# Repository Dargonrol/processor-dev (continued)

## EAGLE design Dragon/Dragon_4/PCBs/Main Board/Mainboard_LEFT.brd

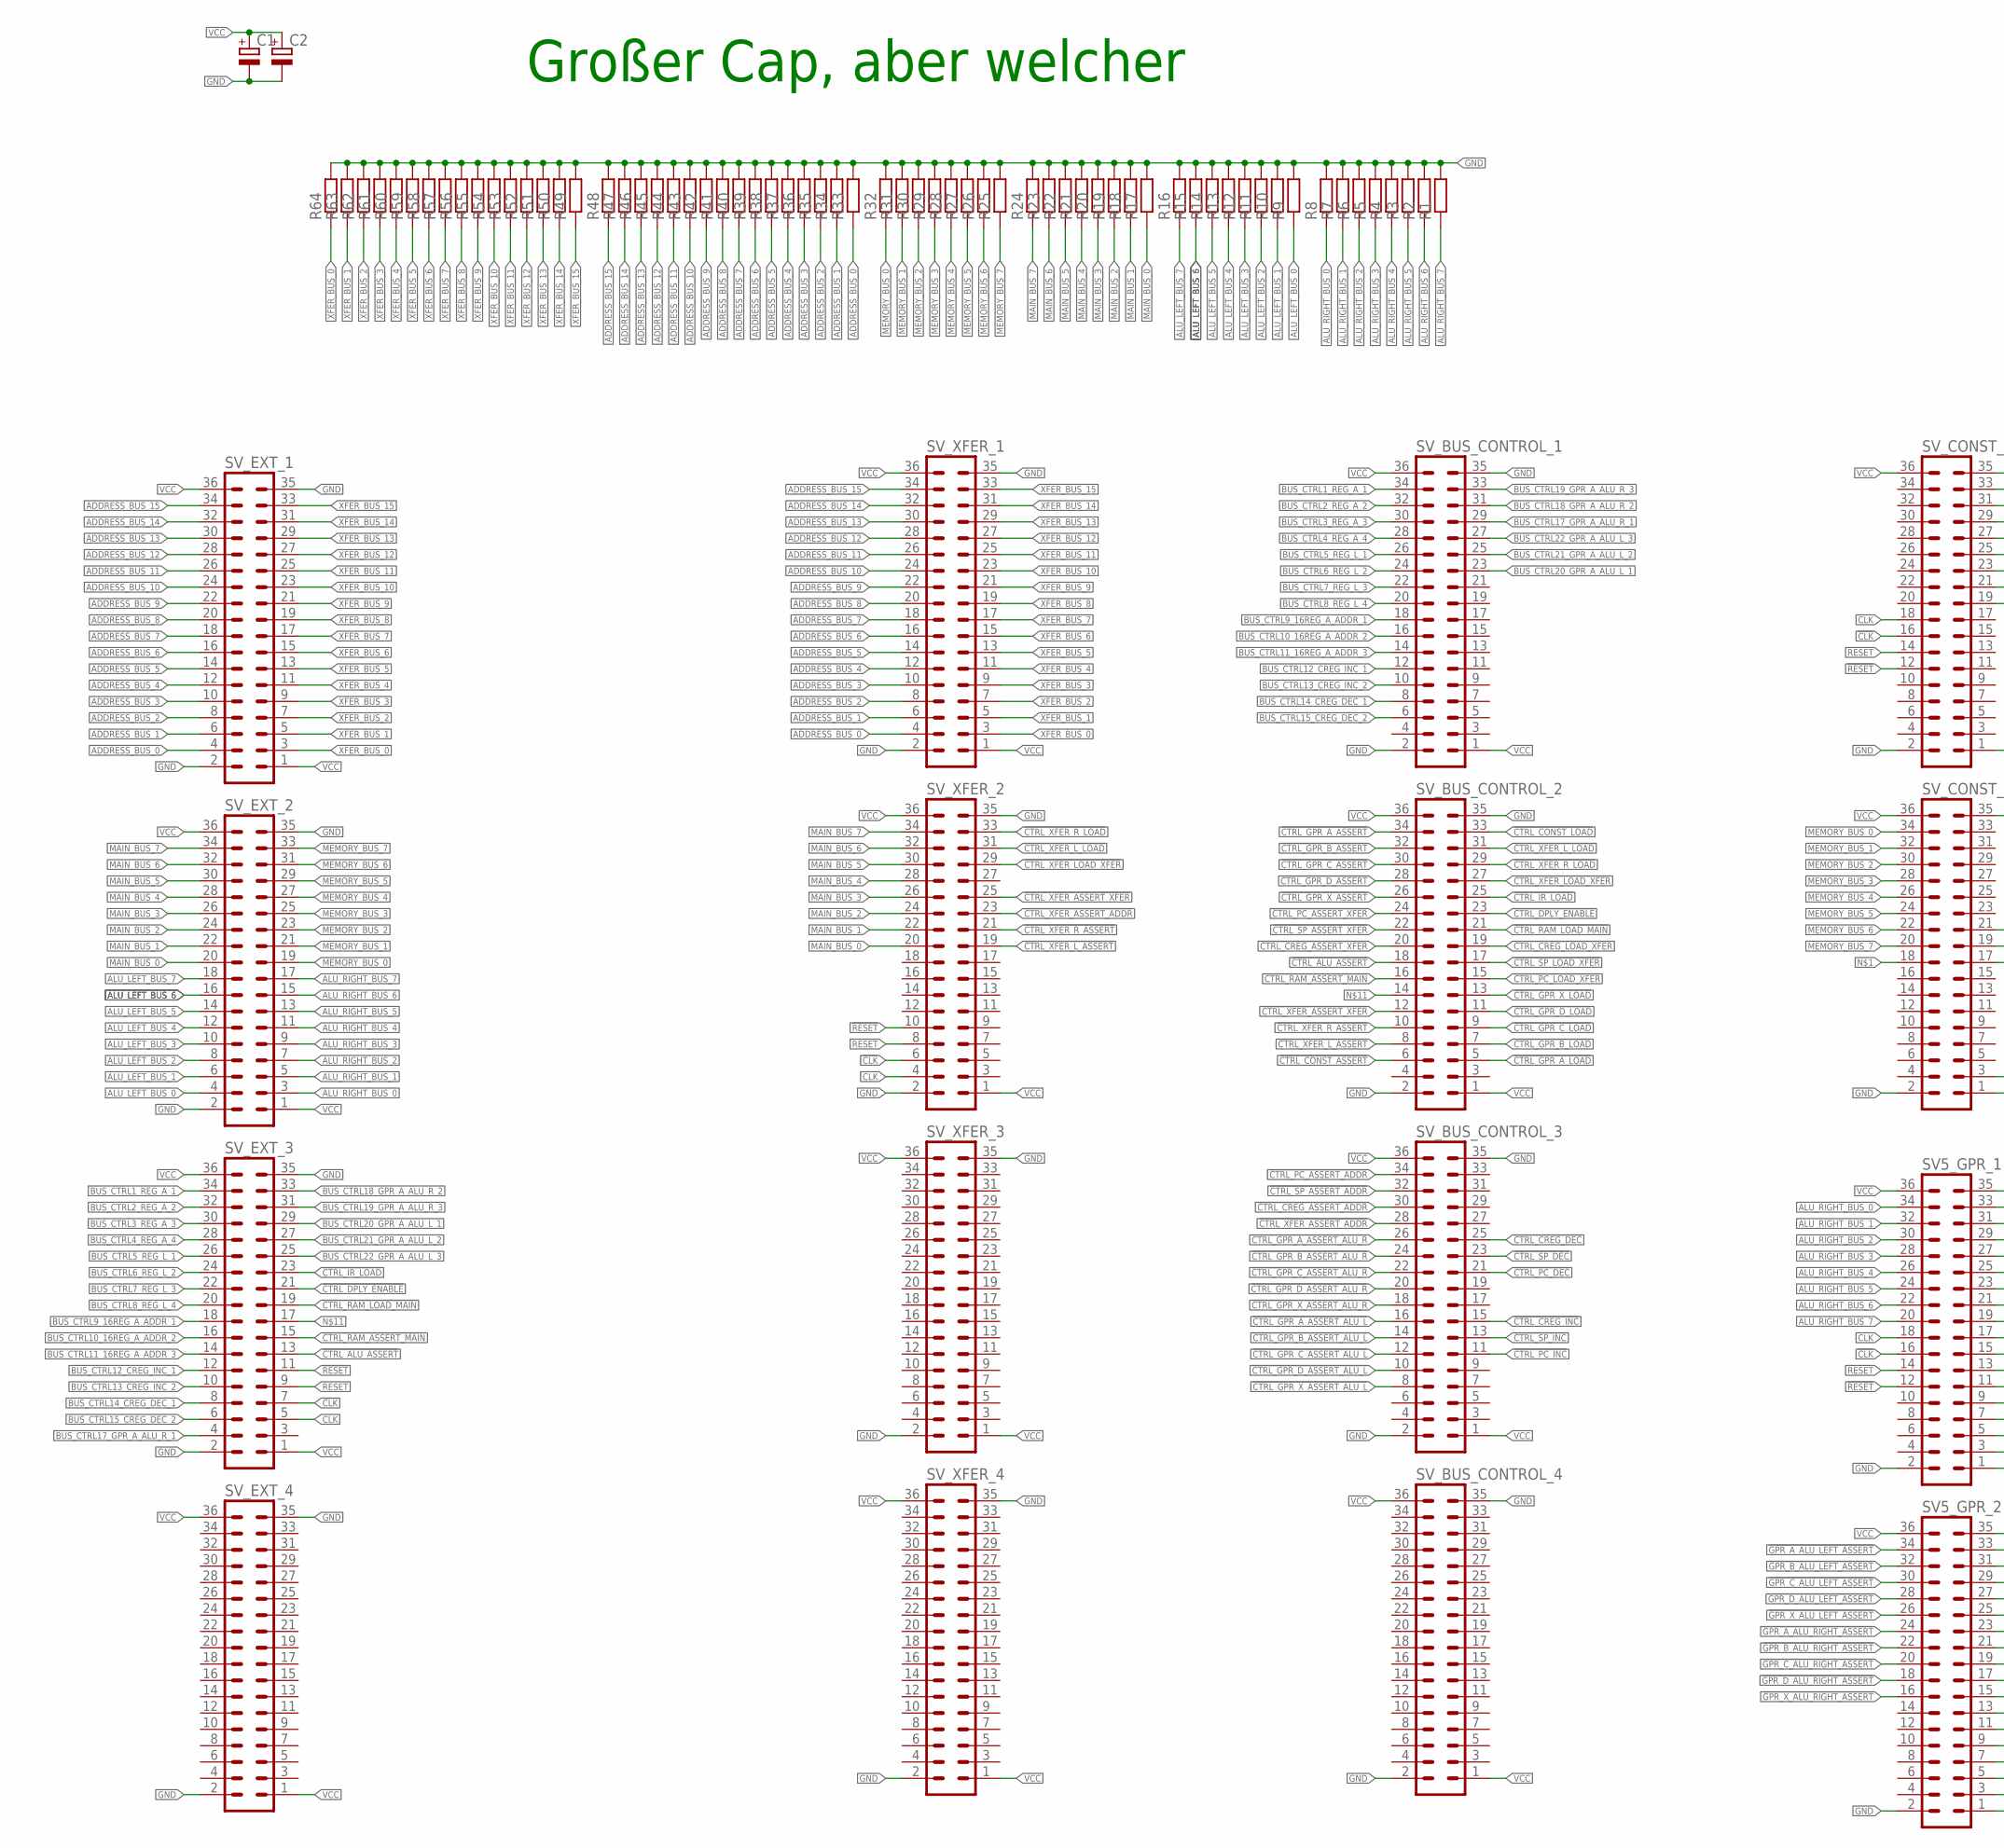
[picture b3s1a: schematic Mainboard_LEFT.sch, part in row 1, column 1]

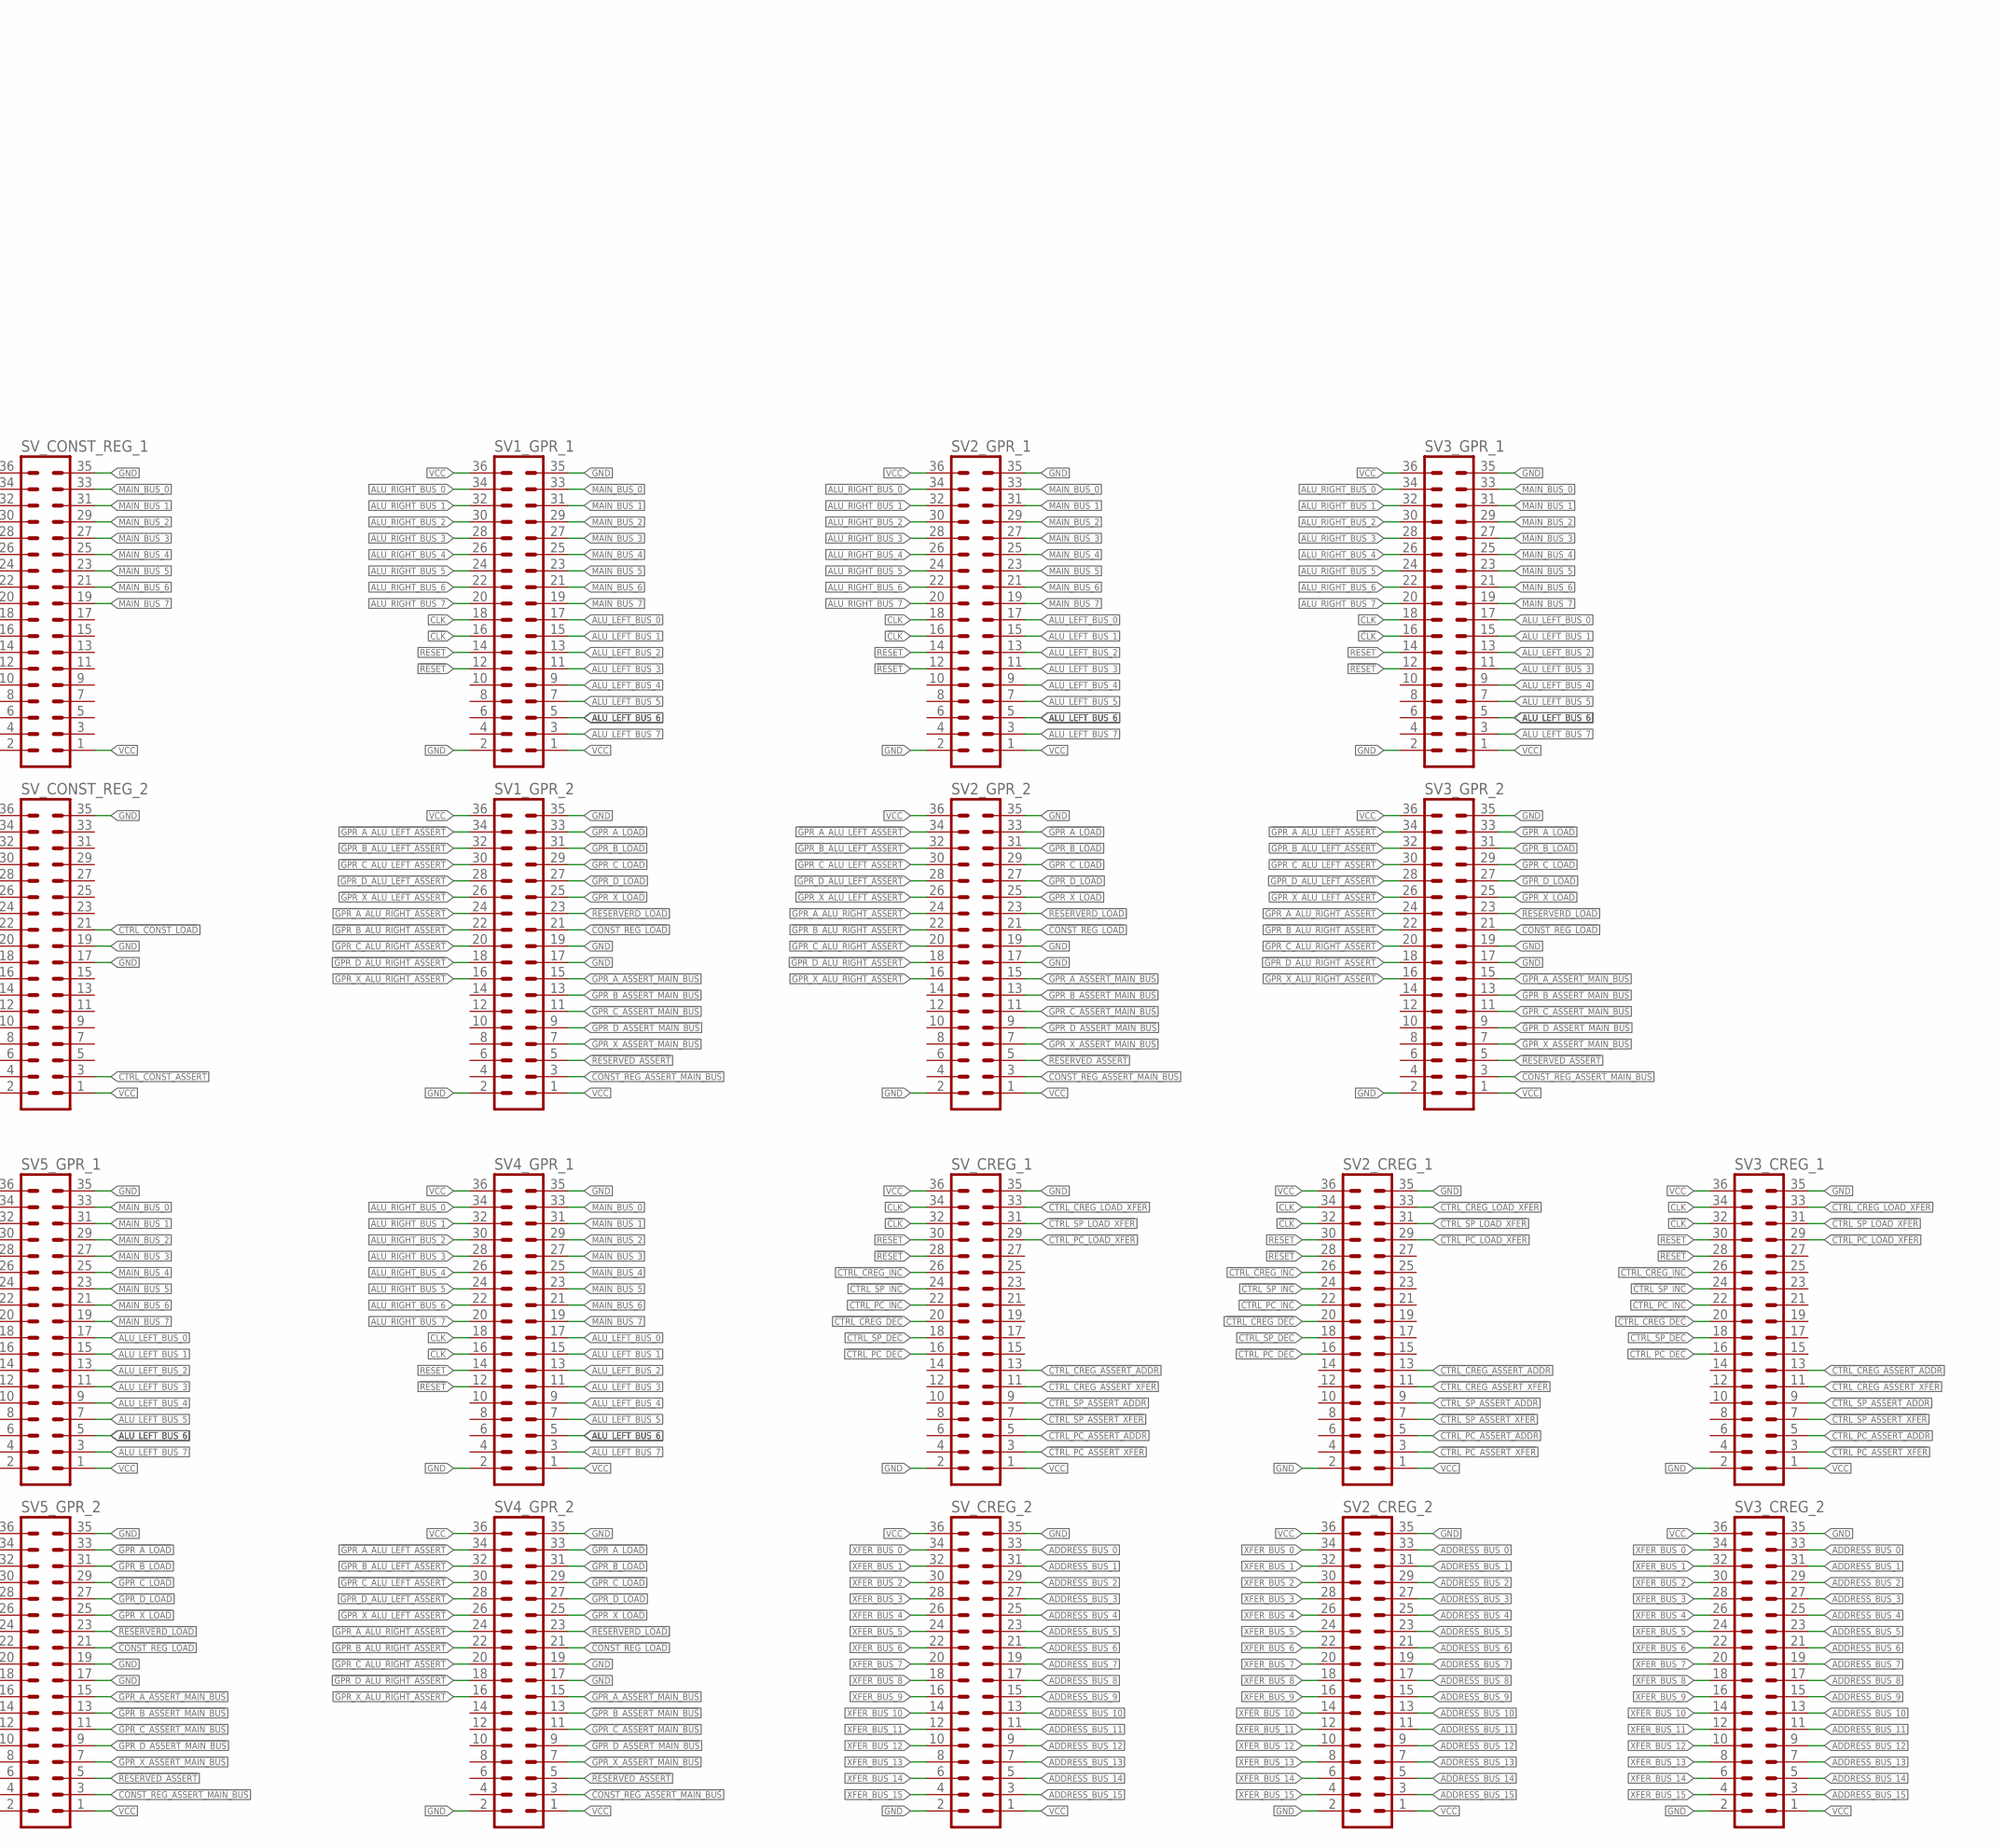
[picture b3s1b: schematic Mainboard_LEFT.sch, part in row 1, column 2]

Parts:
C1, C2: CPOL-EUE5-10.5; E5-10,5
R1, R2, R3, R4, R5, R6, R7, R8, R9, R10, R11, R12, R13, R14, R15, R16, R17, R18, R19, R20, R21, R22, R23, R24, R25, R26, R27, R28, R29, R30, R31, R32, R33, R34, R35, R36, R37, R38, R39, R40, R41, R42, R43, R44, R45, R46, R47, R48, R49, R50, R51, R52, R53, R54, R55, R56, R57, R58, R59, R60, R61, R62, R63, R64: R-EU_R0805; R0805
SV1_GPR_1, SV1_GPR_2, SV2_CREG_1, SV2_CREG_2, SV2_GPR_1, SV2_GPR_2, SV3_CREG_1, SV3_CREG_2, SV3_GPR_1, SV3_GPR_2, SV4_GPR_1, SV4_GPR_2, SV5_GPR_1, SV5_GPR_2: MA18-2
SV_BUS_CONTROL_1, SV_BUS_CONTROL_2, SV_BUS_CONTROL_3, SV_BUS_CONTROL_4: MA18-2
SV_CONST_REG_1, SV_CONST_REG_2: MA18-2
SV_CREG_1, SV_CREG_2: MA18-2
SV_EXT_1, SV_EXT_2, SV_EXT_3, SV_EXT_4: MA18-2W
SV_XFER_1, SV_XFER_2, SV_XFER_3, SV_XFER_4: MA18-2

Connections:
!CLK: SV1_GPR_1.16, SV2_CREG_1.32, SV2_GPR_1.16, SV3_CREG_1.32, SV3_GPR_1.16, SV4_GPR_1.16, SV5_GPR_1.16, SV_CONST_REG_1.16, SV_CREG_1.32, SV_EXT_3.7, SV_XFER_2.6
!CONST_REG_ASSERT_MAIN_BUS: SV1_GPR_2.3, SV2_GPR_2.3, SV3_GPR_2.3, SV4_GPR_2.3, SV5_GPR_2.3
!CONST_REG_LOAD: SV1_GPR_2.21, SV2_GPR_2.21, SV3_GPR_2.21, SV4_GPR_2.21, SV5_GPR_2.21
!CTRL_ALU_ASSERT: SV_BUS_CONTROL_2.18, SV_EXT_3.13
!CTRL_CONST_ASSERT: SV_BUS_CONTROL_2.6, SV_CONST_REG_2.3
!CTRL_CONST_LOAD: SV_BUS_CONTROL_2.33, SV_CONST_REG_2.21
!CTRL_CREG_ASSERT_ADDR: SV2_CREG_1.13, SV3_CREG_1.13, SV_BUS_CONTROL_3.30, SV_CREG_1.13
!CTRL_CREG_ASSERT_XFER: SV2_CREG_1.11, SV3_CREG_1.11, SV_BUS_CONTROL_2.20, SV_CREG_1.11
!CTRL_CREG_DEC: SV2_CREG_1.20, SV3_CREG_1.20, SV_BUS_CONTROL_3.25, SV_CREG_1.20
!CTRL_CREG_INC: SV2_CREG_1.26, SV3_CREG_1.26, SV_BUS_CONTROL_3.15, SV_CREG_1.26
!CTRL_CREG_LOAD_XFER: SV2_CREG_1.33, SV3_CREG_1.33, SV_BUS_CONTROL_2.19, SV_CREG_1.33
!CTRL_DPLY_ENABLE: SV_BUS_CONTROL_2.23, SV_EXT_3.21
!CTRL_GPR_A_ASSERT: SV_BUS_CONTROL_2.34
!CTRL_GPR_A_ASSERT_ALU_L: SV_BUS_CONTROL_3.16
!CTRL_GPR_A_ASSERT_ALU_R: SV_BUS_CONTROL_3.26
!CTRL_GPR_A_LOAD: SV_BUS_CONTROL_2.5
!CTRL_GPR_B_ASSERT: SV_BUS_CONTROL_2.32
!CTRL_GPR_B_ASSERT_ALU_L: SV_BUS_CONTROL_3.14
!CTRL_GPR_B_ASSERT_ALU_R: SV_BUS_CONTROL_3.24
!CTRL_GPR_B_LOAD: SV_BUS_CONTROL_2.7
!CTRL_GPR_C_ASSERT: SV_BUS_CONTROL_2.30
!CTRL_GPR_C_ASSERT_ALU_L: SV_BUS_CONTROL_3.12
!CTRL_GPR_C_ASSERT_ALU_R: SV_BUS_CONTROL_3.22
!CTRL_GPR_C_LOAD: SV_BUS_CONTROL_2.9
!CTRL_GPR_D_ASSERT: SV_BUS_CONTROL_2.28
!CTRL_GPR_D_ASSERT_ALU_L: SV_BUS_CONTROL_3.10
!CTRL_GPR_D_ASSERT_ALU_R: SV_BUS_CONTROL_3.20
!CTRL_GPR_D_LOAD: SV_BUS_CONTROL_2.11
!CTRL_GPR_X_ASSERT: SV_BUS_CONTROL_2.26
!CTRL_GPR_X_ASSERT_ALU_L: SV_BUS_CONTROL_3.8
!CTRL_GPR_X_ASSERT_ALU_R: SV_BUS_CONTROL_3.18
!CTRL_GPR_X_LOAD: SV_BUS_CONTROL_2.13
!CTRL_IR_LOAD: SV_BUS_CONTROL_2.25, SV_EXT_3.23
!CTRL_PC_ASSERT_ADDR: SV2_CREG_1.5, SV3_CREG_1.5, SV_BUS_CONTROL_3.34, SV_CREG_1.5
!CTRL_PC_ASSERT_XFER: SV2_CREG_1.3, SV3_CREG_1.3, SV_BUS_CONTROL_2.24, SV_CREG_1.3
!CTRL_PC_DEC: SV2_CREG_1.16, SV3_CREG_1.16, SV_BUS_CONTROL_3.21, SV_CREG_1.16
!CTRL_PC_INC: SV2_CREG_1.22, SV3_CREG_1.22, SV_BUS_CONTROL_3.11, SV_CREG_1.22
!CTRL_PC_LOAD_XFER: SV2_CREG_1.29, SV3_CREG_1.29, SV_BUS_CONTROL_2.15, SV_CREG_1.29
!CTRL_RAM_ASSERT_MAIN: SV_BUS_CONTROL_2.16, SV_EXT_3.15
!CTRL_RAM_LOAD_MAIN: SV_BUS_CONTROL_2.21, SV_EXT_3.19
!CTRL_SP_ASSERT_ADDR: SV2_CREG_1.9, SV3_CREG_1.9, SV_BUS_CONTROL_3.32, SV_CREG_1.9
!CTRL_SP_ASSERT_XFER: SV2_CREG_1.7, SV3_CREG_1.7, SV_BUS_CONTROL_2.22, SV_CREG_1.7
!CTRL_SP_DEC: SV2_CREG_1.18, SV3_CREG_1.18, SV_BUS_CONTROL_3.23, SV_CREG_1.18
!CTRL_SP_INC: SV2_CREG_1.24, SV3_CREG_1.24, SV_BUS_CONTROL_3.13, SV_CREG_1.24
!CTRL_SP_LOAD_XFER: SV2_CREG_1.31, SV3_CREG_1.31, SV_BUS_CONTROL_2.17, SV_CREG_1.31
!CTRL_XFER_ASSERT_ADDR: SV_BUS_CONTROL_3.28, SV_XFER_2.23
!CTRL_XFER_ASSERT_XFER: SV_BUS_CONTROL_2.12, SV_XFER_2.25
!CTRL_XFER_LOAD_XFER: SV_BUS_CONTROL_2.27, SV_XFER_2.29
!CTRL_XFER_L_ASSERT: SV_BUS_CONTROL_2.8, SV_XFER_2.19
!CTRL_XFER_L_LOAD: SV_BUS_CONTROL_2.31, SV_XFER_2.31
!CTRL_XFER_R_ASSERT: SV_BUS_CONTROL_2.10, SV_XFER_2.21
!CTRL_XFER_R_LOAD: SV_BUS_CONTROL_2.29, SV_XFER_2.33
!GPR_A_ALU_LEFT_ASSERT: SV1_GPR_2.34, SV2_GPR_2.34, SV3_GPR_2.34, SV4_GPR_2.34, SV5_GPR_2.34
!GPR_A_ALU_RIGHT_ASSERT: SV1_GPR_2.24, SV2_GPR_2.24, SV3_GPR_2.24, SV4_GPR_2.24, SV5_GPR_2.24
!GPR_A_ASSERT_MAIN_BUS: SV1_GPR_2.15, SV2_GPR_2.15, SV3_GPR_2.15, SV4_GPR_2.15, SV5_GPR_2.15
!GPR_A_LOAD: SV1_GPR_2.33, SV2_GPR_2.33, SV3_GPR_2.33, SV4_GPR_2.33, SV5_GPR_2.33
!GPR_B_ALU_LEFT_ASSERT: SV1_GPR_2.32, SV2_GPR_2.32, SV3_GPR_2.32, SV4_GPR_2.32, SV5_GPR_2.32
!GPR_B_ALU_RIGHT_ASSERT: SV1_GPR_2.22, SV2_GPR_2.22, SV3_GPR_2.22, SV4_GPR_2.22, SV5_GPR_2.22
!GPR_B_ASSERT_MAIN_BUS: SV1_GPR_2.13, SV2_GPR_2.13, SV3_GPR_2.13, SV4_GPR_2.13, SV5_GPR_2.13
!GPR_B_LOAD: SV1_GPR_2.31, SV2_GPR_2.31, SV3_GPR_2.31, SV4_GPR_2.31, SV5_GPR_2.31
!GPR_C_ALU_LEFT_ASSERT: SV1_GPR_2.30, SV2_GPR_2.30, SV3_GPR_2.30, SV4_GPR_2.30, SV5_GPR_2.30
!GPR_C_ALU_RIGHT_ASSERT: SV1_GPR_2.20, SV2_GPR_2.20, SV3_GPR_2.20, SV4_GPR_2.20, SV5_GPR_2.20
!GPR_C_ASSERT_MAIN_BUS: SV1_GPR_2.11, SV2_GPR_2.11, SV3_GPR_2.11, SV4_GPR_2.11, SV5_GPR_2.11
!GPR_C_LOAD: SV1_GPR_2.29, SV2_GPR_2.29, SV3_GPR_2.29, SV4_GPR_2.29, SV5_GPR_2.29
!GPR_D_ALU_LEFT_ASSERT: SV1_GPR_2.28, SV2_GPR_2.28, SV3_GPR_2.28, SV4_GPR_2.28, SV5_GPR_2.28
!GPR_D_ALU_RIGHT_ASSERT: SV1_GPR_2.18, SV2_GPR_2.18, SV3_GPR_2.18, SV4_GPR_2.18, SV5_GPR_2.18
!GPR_D_ASSERT_MAIN_BUS: SV1_GPR_2.9, SV2_GPR_2.9, SV3_GPR_2.9, SV4_GPR_2.9, SV5_GPR_2.9
!GPR_D_LOAD: SV1_GPR_2.27, SV2_GPR_2.27, SV3_GPR_2.27, SV4_GPR_2.27, SV5_GPR_2.27
!GPR_X_ALU_LEFT_ASSERT: SV1_GPR_2.26, SV2_GPR_2.26, SV3_GPR_2.26, SV4_GPR_2.26, SV5_GPR_2.26
!GPR_X_ALU_RIGHT_ASSERT: SV1_GPR_2.16, SV2_GPR_2.16, SV3_GPR_2.16, SV4_GPR_2.16, SV5_GPR_2.16
!GPR_X_ASSERT_MAIN_BUS: SV1_GPR_2.7, SV2_GPR_2.7, SV3_GPR_2.7, SV4_GPR_2.7, SV5_GPR_2.7
!GPR_X_LOAD: SV1_GPR_2.25, SV2_GPR_2.25, SV3_GPR_2.25, SV4_GPR_2.25, SV5_GPR_2.25
!RESERVED_ASSERT: SV1_GPR_2.5, SV2_GPR_2.5, SV3_GPR_2.5, SV4_GPR_2.5, SV5_GPR_2.5
!RESERVERD_LOAD: SV1_GPR_2.23, SV2_GPR_2.23, SV3_GPR_2.23, SV4_GPR_2.23, SV5_GPR_2.23
!RESET: SV1_GPR_1.12, SV2_CREG_1.28, SV2_GPR_1.12, SV3_CREG_1.28, SV3_GPR_1.12, SV4_GPR_1.12, SV5_GPR_1.12, SV_CONST_REG_1.12, SV_CREG_1.28, SV_EXT_3.11, SV_XFER_2.10
ADDRESS_BUS_0: R33.1, SV2_CREG_2.33, SV3_CREG_2.33, SV_CREG_2.33, SV_EXT_1.4, SV_XFER_1.4
ADDRESS_BUS_1: R34.1, SV2_CREG_2.31, SV3_CREG_2.31, SV_CREG_2.31, SV_EXT_1.6, SV_XFER_1.6
ADDRESS_BUS_2: R35.1, SV2_CREG_2.29, SV3_CREG_2.29, SV_CREG_2.29, SV_EXT_1.8, SV_XFER_1.8
ADDRESS_BUS_3: R36.1, SV2_CREG_2.27, SV3_CREG_2.27, SV_CREG_2.27, SV_EXT_1.10, SV_XFER_1.10
ADDRESS_BUS_4: R37.1, SV2_CREG_2.25, SV3_CREG_2.25, SV_CREG_2.25, SV_EXT_1.12, SV_XFER_1.12
ADDRESS_BUS_5: R38.1, SV2_CREG_2.23, SV3_CREG_2.23, SV_CREG_2.23, SV_EXT_1.14, SV_XFER_1.14
ADDRESS_BUS_6: R39.1, SV2_CREG_2.21, SV3_CREG_2.21, SV_CREG_2.21, SV_EXT_1.16, SV_XFER_1.16
ADDRESS_BUS_7: R40.1, SV2_CREG_2.19, SV3_CREG_2.19, SV_CREG_2.19, SV_EXT_1.18, SV_XFER_1.18
ADDRESS_BUS_8: R41.1, SV2_CREG_2.17, SV3_CREG_2.17, SV_CREG_2.17, SV_EXT_1.20, SV_XFER_1.20
ADDRESS_BUS_9: R42.1, SV2_CREG_2.15, SV3_CREG_2.15, SV_CREG_2.15, SV_EXT_1.22, SV_XFER_1.22
ADDRESS_BUS_10: R43.1, SV2_CREG_2.13, SV3_CREG_2.13, SV_CREG_2.13, SV_EXT_1.24, SV_XFER_1.24
ADDRESS_BUS_11: R44.1, SV2_CREG_2.11, SV3_CREG_2.11, SV_CREG_2.11, SV_EXT_1.26, SV_XFER_1.26
ADDRESS_BUS_12: R45.1, SV2_CREG_2.9, SV3_CREG_2.9, SV_CREG_2.9, SV_EXT_1.28, SV_XFER_1.28
ADDRESS_BUS_13: R46.1, SV2_CREG_2.7, SV3_CREG_2.7, SV_CREG_2.7, SV_EXT_1.30, SV_XFER_1.30
ADDRESS_BUS_14: R47.1, SV2_CREG_2.5, SV3_CREG_2.5, SV_CREG_2.5, SV_EXT_1.32, SV_XFER_1.32
ADDRESS_BUS_15: R48.1, SV2_CREG_2.3, SV3_CREG_2.3, SV_CREG_2.3, SV_EXT_1.34, SV_XFER_1.34
ALU_LEFT_BUS_0: R9.1, SV1_GPR_1.17, SV2_GPR_1.17, SV3_GPR_1.17, SV4_GPR_1.17, SV5_GPR_1.17, SV_EXT_2.4
ALU_LEFT_BUS_1: R10.1, SV1_GPR_1.15, SV2_GPR_1.15, SV3_GPR_1.15, SV4_GPR_1.15, SV5_GPR_1.15, SV_EXT_2.6
ALU_LEFT_BUS_2: R11.1, SV1_GPR_1.13, SV2_GPR_1.13, SV3_GPR_1.13, SV4_GPR_1.13, SV5_GPR_1.13, SV_EXT_2.8
ALU_LEFT_BUS_3: R12.1, SV1_GPR_1.11, SV2_GPR_1.11, SV3_GPR_1.11, SV4_GPR_1.11, SV5_GPR_1.11, SV_EXT_2.10
ALU_LEFT_BUS_4: R13.1, SV1_GPR_1.9, SV2_GPR_1.9, SV3_GPR_1.9, SV4_GPR_1.9, SV5_GPR_1.9, SV_EXT_2.12
ALU_LEFT_BUS_5: R14.1, SV1_GPR_1.7, SV2_GPR_1.7, SV3_GPR_1.7, SV4_GPR_1.7, SV5_GPR_1.7, SV_EXT_2.14
ALU_LEFT_BUS_6: R15.1, SV1_GPR_1.5, SV2_GPR_1.5, SV3_GPR_1.5, SV4_GPR_1.5, SV5_GPR_1.5, SV_EXT_2.16
ALU_LEFT_BUS_7: R16.1, SV1_GPR_1.3, SV2_GPR_1.3, SV3_GPR_1.3, SV4_GPR_1.3, SV5_GPR_1.3, SV_EXT_2.18
ALU_RIGHT_BUS_0: R8.1, SV1_GPR_1.34, SV2_GPR_1.34, SV3_GPR_1.34, SV4_GPR_1.34, SV5_GPR_1.34, SV_EXT_2.3
ALU_RIGHT_BUS_1: R7.1, SV1_GPR_1.32, SV2_GPR_1.32, SV3_GPR_1.32, SV4_GPR_1.32, SV5_GPR_1.32, SV_EXT_2.5
ALU_RIGHT_BUS_2: R6.1, SV1_GPR_1.30, SV2_GPR_1.30, SV3_GPR_1.30, SV4_GPR_1.30, SV5_GPR_1.30, SV_EXT_2.7
ALU_RIGHT_BUS_3: R5.1, SV1_GPR_1.28, SV2_GPR_1.28, SV3_GPR_1.28, SV4_GPR_1.28, SV5_GPR_1.28, SV_EXT_2.9
ALU_RIGHT_BUS_4: R4.1, SV1_GPR_1.26, SV2_GPR_1.26, SV3_GPR_1.26, SV4_GPR_1.26, SV5_GPR_1.26, SV_EXT_2.11
ALU_RIGHT_BUS_5: R3.1, SV1_GPR_1.24, SV2_GPR_1.24, SV3_GPR_1.24, SV4_GPR_1.24, SV5_GPR_1.24, SV_EXT_2.13
ALU_RIGHT_BUS_6: R2.1, SV1_GPR_1.22, SV2_GPR_1.22, SV3_GPR_1.22, SV4_GPR_1.22, SV5_GPR_1.22, SV_EXT_2.15
ALU_RIGHT_BUS_7: R1.1, SV1_GPR_1.20, SV2_GPR_1.20, SV3_GPR_1.20, SV4_GPR_1.20, SV5_GPR_1.20, SV_EXT_2.17
BUS_CTRL1_REG_A_1: SV_BUS_CONTROL_1.34, SV_EXT_3.34
BUS_CTRL2_REG_A_2: SV_BUS_CONTROL_1.32, SV_EXT_3.32
BUS_CTRL3_REG_A_3: SV_BUS_CONTROL_1.30, SV_EXT_3.30
BUS_CTRL4_REG_A_4: SV_BUS_CONTROL_1.28, SV_EXT_3.28
BUS_CTRL5_REG_L_1: SV_BUS_CONTROL_1.26, SV_EXT_3.26
BUS_CTRL6_REG_L_2: SV_BUS_CONTROL_1.24, SV_EXT_3.24
BUS_CTRL7_REG_L_3: SV_BUS_CONTROL_1.22, SV_EXT_3.22
BUS_CTRL8_REG_L_4: SV_BUS_CONTROL_1.20, SV_EXT_3.20
BUS_CTRL9_16REG_A_ADDR_1: SV_BUS_CONTROL_1.18, SV_EXT_3.18
BUS_CTRL10_16REG_A_ADDR_2: SV_BUS_CONTROL_1.16, SV_EXT_3.16
BUS_CTRL11_16REG_A_ADDR_3: SV_BUS_CONTROL_1.14, SV_EXT_3.14
BUS_CTRL12_CREG_INC_1: SV_BUS_CONTROL_1.12, SV_EXT_3.12
BUS_CTRL13_CREG_INC_2: SV_BUS_CONTROL_1.10, SV_EXT_3.10
BUS_CTRL14_CREG_DEC_1: SV_BUS_CONTROL_1.8, SV_EXT_3.8
BUS_CTRL15_CREG_DEC_2: SV_BUS_CONTROL_1.6, SV_EXT_3.6
BUS_CTRL17_GPR_A_ALU_R_1: SV_BUS_CONTROL_1.29, SV_EXT_3.4
BUS_CTRL18_GPR_A_ALU_R_2: SV_BUS_CONTROL_1.31, SV_EXT_3.33
BUS_CTRL19_GPR_A_ALU_R_3: SV_BUS_CONTROL_1.33, SV_EXT_3.31
BUS_CTRL20_GPR_A_ALU_L_1: SV_BUS_CONTROL_1.23, SV_EXT_3.29
BUS_CTRL21_GPR_A_ALU_L_2: SV_BUS_CONTROL_1.25, SV_EXT_3.27
BUS_CTRL22_GPR_A_ALU_L_3: SV_BUS_CONTROL_1.27, SV_EXT_3.25
CLK: SV1_GPR_1.18, SV2_CREG_1.34, SV2_GPR_1.18, SV3_CREG_1.34, SV3_GPR_1.18, SV4_GPR_1.18, SV5_GPR_1.18, SV_CONST_REG_1.18, SV_CREG_1.34, SV_EXT_3.5, SV_XFER_2.4
GND: C1.-, C2.-, R1.2, R2.2, R3.2, R4.2, R5.2, R6.2, R7.2, R8.2, R9.2, R10.2, R11.2, R12.2, R13.2, R14.2, R15.2, R16.2, R17.2, R18.2, R19.2, R20.2, R21.2, R22.2, R23.2, R24.2, R25.2, R26.2, R27.2, R28.2, R29.2, R30.2, R31.2, R32.2, R33.2, R34.2, R35.2, R36.2, R37.2, R38.2, R39.2, R40.2, R41.2, R42.2, R43.2, R44.2, R45.2, R46.2, R47.2, R48.2, R49.2, R50.2, R51.2, R52.2, R53.2, R54.2, R55.2, R56.2, R57.2, R58.2, R59.2, R60.2, R61.2, R62.2, R63.2, R64.2, SV1_GPR_1.2, SV1_GPR_1.35, SV1_GPR_2.2, SV1_GPR_2.17, SV1_GPR_2.19, SV1_GPR_2.35, SV2_CREG_1.2, SV2_CREG_1.35, SV2_CREG_2.2, SV2_CREG_2.35, SV2_GPR_1.2, SV2_GPR_1.35, SV2_GPR_2.2, SV2_GPR_2.17, SV2_GPR_2.19, SV2_GPR_2.35, SV3_CREG_1.2, SV3_CREG_1.35, SV3_CREG_2.2, SV3_CREG_2.35, SV3_GPR_1.2, SV3_GPR_1.35, SV3_GPR_2.2, SV3_GPR_2.17, SV3_GPR_2.19, SV3_GPR_2.35, SV4_GPR_1.2, SV4_GPR_1.35, SV4_GPR_2.2, SV4_GPR_2.17, SV4_GPR_2.19, SV4_GPR_2.35, SV5_GPR_1.2, SV5_GPR_1.35, SV5_GPR_2.2, SV5_GPR_2.17, SV5_GPR_2.19, SV5_GPR_2.35, SV_BUS_CONTROL_1.2, SV_BUS_CONTROL_1.35, SV_BUS_CONTROL_2.2, SV_BUS_CONTROL_2.35, SV_BUS_CONTROL_3.2, SV_BUS_CONTROL_3.35, SV_BUS_CONTROL_4.2, SV_BUS_CONTROL_4.35, SV_CONST_REG_1.2, SV_CONST_REG_1.35, SV_CONST_REG_2.2, SV_CONST_REG_2.17, SV_CONST_REG_2.19, SV_CONST_REG_2.35, SV_CREG_1.2, SV_CREG_1.35, SV_CREG_2.2, SV_CREG_2.35, SV_EXT_1.2, SV_EXT_1.35, SV_EXT_2.2, SV_EXT_2.35, SV_EXT_3.2, SV_EXT_3.35, SV_EXT_4.2, SV_EXT_4.35, SV_XFER_1.2, SV_XFER_1.35, SV_XFER_2.2, SV_XFER_2.35, SV_XFER_3.2, SV_XFER_3.35, SV_XFER_4.2, SV_XFER_4.35
MAIN_BUS_0: R17.1, SV1_GPR_1.33, SV2_GPR_1.33, SV3_GPR_1.33, SV4_GPR_1.33, SV5_GPR_1.33, SV_CONST_REG_1.33, SV_EXT_2.20, SV_XFER_2.20
MAIN_BUS_1: R18.1, SV1_GPR_1.31, SV2_GPR_1.31, SV3_GPR_1.31, SV4_GPR_1.31, SV5_GPR_1.31, SV_CONST_REG_1.31, SV_EXT_2.22, SV_XFER_2.22
MAIN_BUS_2: R19.1, SV1_GPR_1.29, SV2_GPR_1.29, SV3_GPR_1.29, SV4_GPR_1.29, SV5_GPR_1.29, SV_CONST_REG_1.29, SV_EXT_2.24, SV_XFER_2.24
MAIN_BUS_3: R20.1, SV1_GPR_1.27, SV2_GPR_1.27, SV3_GPR_1.27, SV4_GPR_1.27, SV5_GPR_1.27, SV_CONST_REG_1.27, SV_EXT_2.26, SV_XFER_2.26
MAIN_BUS_4: R21.1, SV1_GPR_1.25, SV2_GPR_1.25, SV3_GPR_1.25, SV4_GPR_1.25, SV5_GPR_1.25, SV_CONST_REG_1.25, SV_EXT_2.28, SV_XFER_2.28
MAIN_BUS_5: R22.1, SV1_GPR_1.23, SV2_GPR_1.23, SV3_GPR_1.23, SV4_GPR_1.23, SV5_GPR_1.23, SV_CONST_REG_1.23, SV_EXT_2.30, SV_XFER_2.30
MAIN_BUS_6: R23.1, SV1_GPR_1.21, SV2_GPR_1.21, SV3_GPR_1.21, SV4_GPR_1.21, SV5_GPR_1.21, SV_CONST_REG_1.21, SV_EXT_2.32, SV_XFER_2.32
MAIN_BUS_7: R24.1, SV1_GPR_1.19, SV2_GPR_1.19, SV3_GPR_1.19, SV4_GPR_1.19, SV5_GPR_1.19, SV_CONST_REG_1.19, SV_EXT_2.34, SV_XFER_2.34
MEMORY_BUS_0: R32.1, SV_CONST_REG_2.34, SV_EXT_2.19
MEMORY_BUS_1: R31.1, SV_CONST_REG_2.32, SV_EXT_2.21
MEMORY_BUS_2: R30.1, SV_CONST_REG_2.30, SV_EXT_2.23
MEMORY_BUS_3: R29.1, SV_CONST_REG_2.28, SV_EXT_2.25
MEMORY_BUS_4: R28.1, SV_CONST_REG_2.26, SV_EXT_2.27
MEMORY_BUS_5: R27.1, SV_CONST_REG_2.24, SV_EXT_2.29
MEMORY_BUS_6: R26.1, SV_CONST_REG_2.22, SV_EXT_2.31
MEMORY_BUS_7: R25.1, SV_CONST_REG_2.20, SV_EXT_2.33
unnamed: SV_BUS_CONTROL_2.14, SV_EXT_3.17
RESET: SV1_GPR_1.14, SV2_CREG_1.30, SV2_GPR_1.14, SV3_CREG_1.30, SV3_GPR_1.14, SV4_GPR_1.14, SV5_GPR_1.14, SV_CONST_REG_1.14, SV_CREG_1.30, SV_EXT_3.9, SV_XFER_2.8
VCC: C1.+, C2.+, SV1_GPR_1.1, SV1_GPR_1.36, SV1_GPR_2.1, SV1_GPR_2.36, SV2_CREG_1.1, SV2_CREG_1.36, SV2_CREG_2.1, SV2_CREG_2.36, SV2_GPR_1.1, SV2_GPR_1.36, SV2_GPR_2.1, SV2_GPR_2.36, SV3_CREG_1.1, SV3_CREG_1.36, SV3_CREG_2.1, SV3_CREG_2.36, SV3_GPR_1.1, SV3_GPR_1.36, SV3_GPR_2.1, SV3_GPR_2.36, SV4_GPR_1.1, SV4_GPR_1.36, SV4_GPR_2.1, SV4_GPR_2.36, SV5_GPR_1.1, SV5_GPR_1.36, SV5_GPR_2.1, SV5_GPR_2.36, SV_BUS_CONTROL_1.1, SV_BUS_CONTROL_1.36, SV_BUS_CONTROL_2.1, SV_BUS_CONTROL_2.36, SV_BUS_CONTROL_3.1, SV_BUS_CONTROL_3.36, SV_BUS_CONTROL_4.1, SV_BUS_CONTROL_4.36, SV_CONST_REG_1.1, SV_CONST_REG_1.36, SV_CONST_REG_2.1, SV_CONST_REG_2.36, SV_CREG_1.1, SV_CREG_1.36, SV_CREG_2.1, SV_CREG_2.36, SV_EXT_1.1, SV_EXT_1.36, SV_EXT_2.1, SV_EXT_2.36, SV_EXT_3.1, SV_EXT_3.36, SV_EXT_4.1, SV_EXT_4.36, SV_XFER_1.1, SV_XFER_1.36, SV_XFER_2.1, SV_XFER_2.36, SV_XFER_3.1, SV_XFER_3.36, SV_XFER_4.1, SV_XFER_4.36
XFER_BUS_0: R64.1, SV2_CREG_2.34, SV3_CREG_2.34, SV_CREG_2.34, SV_EXT_1.3, SV_XFER_1.3
XFER_BUS_1: R63.1, SV2_CREG_2.32, SV3_CREG_2.32, SV_CREG_2.32, SV_EXT_1.5, SV_XFER_1.5
XFER_BUS_2: R62.1, SV2_CREG_2.30, SV3_CREG_2.30, SV_CREG_2.30, SV_EXT_1.7, SV_XFER_1.7
XFER_BUS_3: R61.1, SV2_CREG_2.28, SV3_CREG_2.28, SV_CREG_2.28, SV_EXT_1.9, SV_XFER_1.9
XFER_BUS_4: R60.1, SV2_CREG_2.26, SV3_CREG_2.26, SV_CREG_2.26, SV_EXT_1.11, SV_XFER_1.11
XFER_BUS_5: R59.1, SV2_CREG_2.24, SV3_CREG_2.24, SV_CREG_2.24, SV_EXT_1.13, SV_XFER_1.13
XFER_BUS_6: R58.1, SV2_CREG_2.22, SV3_CREG_2.22, SV_CREG_2.22, SV_EXT_1.15, SV_XFER_1.15
XFER_BUS_7: R57.1, SV2_CREG_2.20, SV3_CREG_2.20, SV_CREG_2.20, SV_EXT_1.17, SV_XFER_1.17
XFER_BUS_8: R56.1, SV2_CREG_2.18, SV3_CREG_2.18, SV_CREG_2.18, SV_EXT_1.19, SV_XFER_1.19
XFER_BUS_9: R55.1, SV2_CREG_2.16, SV3_CREG_2.16, SV_CREG_2.16, SV_EXT_1.21, SV_XFER_1.21
XFER_BUS_10: R54.1, SV2_CREG_2.14, SV3_CREG_2.14, SV_CREG_2.14, SV_EXT_1.23, SV_XFER_1.23
XFER_BUS_11: R53.1, SV2_CREG_2.12, SV3_CREG_2.12, SV_CREG_2.12, SV_EXT_1.25, SV_XFER_1.25
XFER_BUS_12: R52.1, SV2_CREG_2.10, SV3_CREG_2.10, SV_CREG_2.10, SV_EXT_1.27, SV_XFER_1.27
XFER_BUS_13: R51.1, SV2_CREG_2.8, SV3_CREG_2.8, SV_CREG_2.8, SV_EXT_1.29, SV_XFER_1.29
XFER_BUS_14: R50.1, SV2_CREG_2.6, SV3_CREG_2.6, SV_CREG_2.6, SV_EXT_1.31, SV_XFER_1.31
XFER_BUS_15: R49.1, SV2_CREG_2.4, SV3_CREG_2.4, SV_CREG_2.4, SV_EXT_1.33, SV_XFER_1.33

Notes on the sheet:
Großer Cap, aber welcher

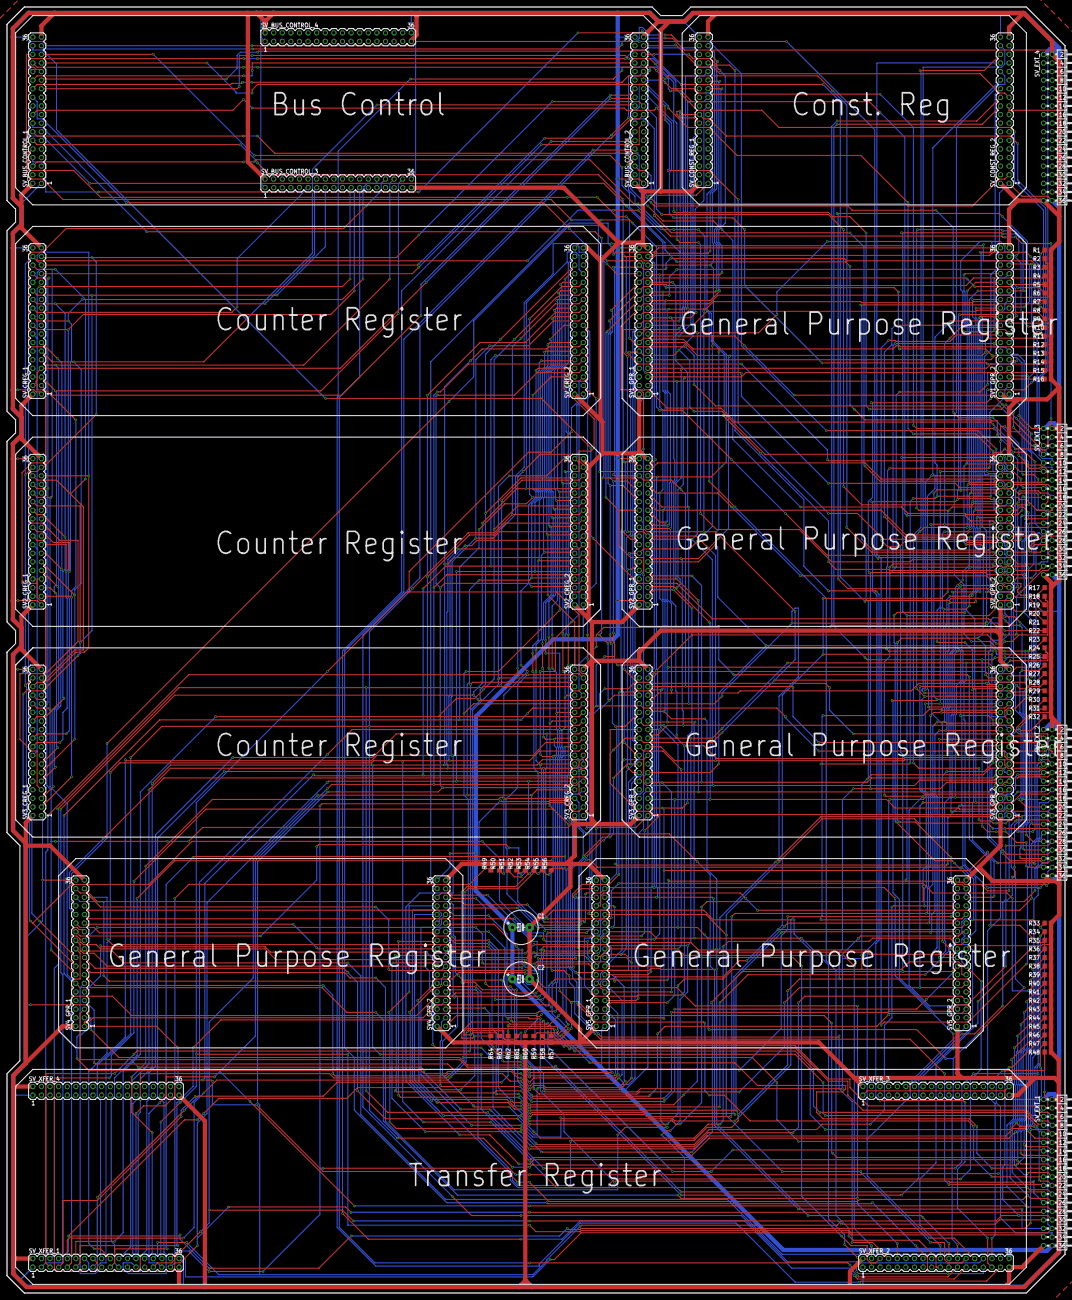
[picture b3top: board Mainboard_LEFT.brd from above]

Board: 2 copper layers, 312.4 x 379.7 mm, 96 parts (0 on the bottom side), 145 nets.
